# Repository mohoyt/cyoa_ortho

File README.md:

# CYOA (Choose Your Own Adventure) Ortho

CYOA Ortho or Choose Your Own Adventure Ortho is a simple Pro Micro compatible ortho PCB that you can freely adjust to your preferences by snapping off rows or columns to make your perfect Ortho board. 

The board is a 5 row x 12 column board to begin with but with the perforations on the board you can make it almost any size down to 3 x 3. So you can build ortho layouts like the Preonic (5x12), Planck (4x12), Gherkin (3x10) or even a macro or num pad.

If you go with a 4 or a 5 row variant then you have the option to have 1 or 2 2u keys on the bottom row too.

A single optional rotary encoder can be added in one of 8 positions. Supports MX or choc v1 (and v2 (since CYOA v0.4)) switches. 

See the KLE layout here: [http://www.keyboard-layout-editor.com/#/gists/a172a36ed405e7bec95fd89415a75808](http://www.keyboard-layout-editor.com/#/gists/a172a36ed405e7bec95fd89415a75808)

## Where to get one

Limited PCBs are available at STHLM kb: [https://sthlmkb.com/shop/cyoa-ortho/](https://sthlmkb.com/shop/cyoa-ortho/)

## Build instructions

These are printed on the PCB. The build is pretty simple.

1. Decide what size board you want
2. Carefully snap along perforations on PCB. It helps to use a flush cutter to help start at each end and then to use the edge of a table to assist with bending and snapping. FR4 is sharp so be careful and make sure to sand or file the edges to smoothen them
3. Solder the diodes (either side is technically fine) just make sure that you have the right orientation for them. The black stripe on the diode should line up with the white stripe on the top of the board
4. Solder the 2 switches directly above the controller. Trim the pins and isolate them with electrical tape after so that they do not short on the controller.
5. Flash and solder the controller onto the board. You want the controller to be as close as possible to the board so that it doesn't clash with any case that you're using. Make sure to plug in the board and test all the switch contacts (e.g. with tweezers) once you have done this. 
6. Install stabilisers (if you're using them), encoder (again, if you're using one) and      switches on the rest of the board.
7. Install in case. Enjoy.  

## Flashing instructions

See the firmware folder for more information.

There are example qmk files for 5x12 and 4x12 layouts for both QMK and Vial setups. These will need to be compiled using QMK or the Vial fork of Vial respectively. The `info.json` file contains all possible layouts so it should be possible to easily craft your layout using that as a starting point. 

## Plates

The CYOA Ortho is a bare PCB with no plate. It is theoretically possible to make a plate for it, and probably not hard either since it is a grid. A plate for a Planck or a Preonic could also be used if you have the same size.

## Cases

3d printed cases are available for CYOA Ortho. See here for more details: [https://www.printables.com/model/784492-cyoa-choose-your-own-adventure-ortho-keyboard-case](https://www.printables.com/model/784492-cyoa-choose-your-own-adventure-ortho-keyboard-case) These are tray style and attach to the M2 holes on the PCB. Cases are available for all possible size variations.

## Changelog / known issues

- Version 0.1 had the wrong size Pro Micro footprint. This is updated in v0.2
- Version 0.2 had a trace not connected fully meaning that the four leftmost keys on the 4th row would not work. This is fixed in version 0.3
- Version 0.4 now has larger centre holes for Choc v2 switches (currently untested though)

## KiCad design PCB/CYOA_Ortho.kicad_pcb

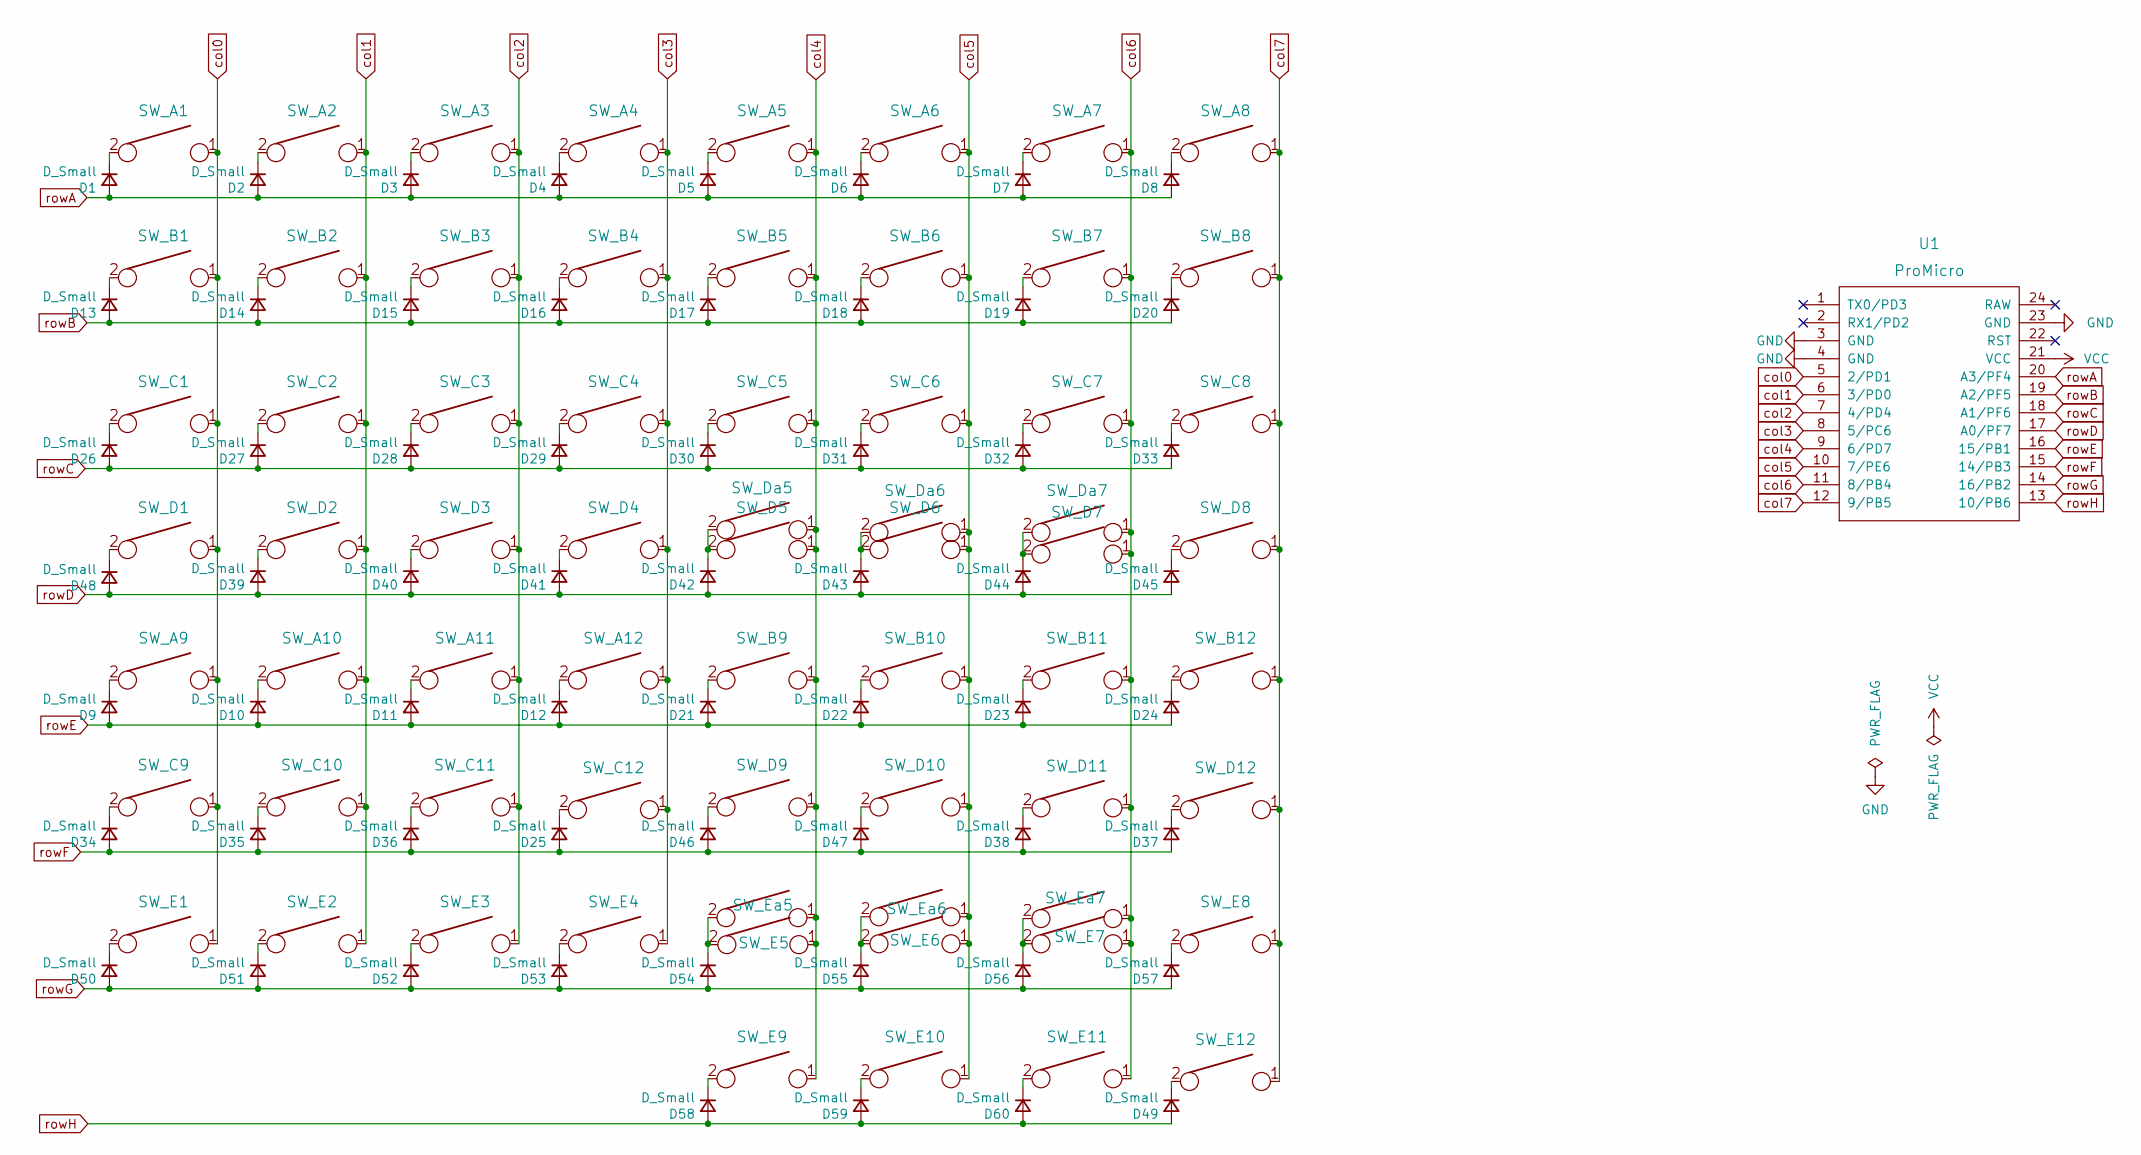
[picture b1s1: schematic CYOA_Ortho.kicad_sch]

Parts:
D1, D2, D3, D4, D5, D6, D7, D8, D9, D10, D11, D12, D13, D14, D15, D16, D17, D18, D19, D20, D21, D22, D23, D24, D25, D26, D27, D28, D29, D30, D31, D32, D33, D34, D35, D36, D37, D38, D39, D40, D41, D42, D43, D44, D45, D46, D47, D48, D49, D50, D51, D52, D53, D54, D55, D56, D57, D58, D59, D60: D_Small; Diode-Hybrid-Back
SW_A1, SW_A2, SW_A3, SW_A4, SW_A5, SW_A6, SW_A7, SW_A8, SW_A9, SW_A10, SW_A11, SW_A12: KEYSW; MX-Alps-Choc-1U-NoLED
SW_B1, SW_B2, SW_B3, SW_B4, SW_B5, SW_B6, SW_B7, SW_B8, SW_B9, SW_B10, SW_B11, SW_B12: KEYSW; MX-Alps-Choc-1U-NoLED
SW_C1, SW_C2, SW_C3, SW_C4, SW_C5, SW_C6, SW_C7, SW_C8, SW_C9, SW_C10, SW_C11, SW_C12: KEYSW; MX-Alps-Choc-1U-NoLED
SW_D1, SW_D2, SW_D3, SW_D4, SW_D5, SW_D6, SW_D7, SW_D8, SW_D9, SW_D10, SW_D11, SW_D12: KEYSW; MX-Alps-Choc-1U-NoLED
SW_Da5, SW_Da6, SW_Da7: KEYSW; MX-Alps-Choc-2U-StabFlip-NoLED
SW_E1, SW_E2, SW_E3, SW_E4, SW_E5, SW_E6, SW_E7, SW_E8, SW_E9, SW_E10, SW_E11, SW_E12: KEYSW; MX-Alps-Choc-1U-NoLED
SW_Ea5, SW_Ea6, SW_Ea7: KEYSW; MX-Alps-Choc-2U-StabFlip-NoLED
U1: ProMicro; ArduinoProMicro-Mini-USB

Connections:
GND: U1.3 (GND), U1.4 (GND), U1.23 (GND)
unnamed: D1.1 (K), SW_A1.2
unnamed: D2.1 (K), SW_A2.2
unnamed: D3.1 (K), SW_A3.2
unnamed: D4.1 (K), SW_A4.2
unnamed: D5.1 (K), SW_A5.2
unnamed: D6.1 (K), SW_A6.2
unnamed: D7.1 (K), SW_A7.2
unnamed: D8.1 (K), SW_A8.2
unnamed: D9.1 (K), SW_A9.2
unnamed: D10.1 (K), SW_A10.2
unnamed: D11.1 (K), SW_A11.2
unnamed: D12.1 (K), SW_A12.2
unnamed: D13.1 (K), SW_B1.2
unnamed: D14.1 (K), SW_B2.2
unnamed: D15.1 (K), SW_B3.2
unnamed: D16.1 (K), SW_B4.2
unnamed: D17.1 (K), SW_B5.2
unnamed: D18.1 (K), SW_B6.2
unnamed: D19.1 (K), SW_B7.2
unnamed: D20.1 (K), SW_B8.2
unnamed: D21.1 (K), SW_B9.2
unnamed: D22.1 (K), SW_B10.2
unnamed: D23.1 (K), SW_B11.2
unnamed: D24.1 (K), SW_B12.2
unnamed: D25.1 (K), SW_C12.2
unnamed: D26.1 (K), SW_C1.2
unnamed: D27.1 (K), SW_C2.2
unnamed: D28.1 (K), SW_C3.2
unnamed: D29.1 (K), SW_C4.2
unnamed: D30.1 (K), SW_C5.2
unnamed: D31.1 (K), SW_C6.2
unnamed: D32.1 (K), SW_C7.2
unnamed: D33.1 (K), SW_C8.2
unnamed: D34.1 (K), SW_C9.2
unnamed: D35.1 (K), SW_C10.2
unnamed: D36.1 (K), SW_C11.2
unnamed: D37.1 (K), SW_D12.2
unnamed: D38.1 (K), SW_D11.2
unnamed: D39.1 (K), SW_D2.2
unnamed: D40.1 (K), SW_D3.2
unnamed: D41.1 (K), SW_D4.2
unnamed: D42.1 (K), SW_D5.2, SW_Da5.2
unnamed: D43.1 (K), SW_D6.2, SW_Da6.2
unnamed: D44.1 (K), SW_D7.2, SW_Da7.2
unnamed: D45.1 (K), SW_D8.2
unnamed: D46.1 (K), SW_D9.2
unnamed: D47.1 (K), SW_D10.2
unnamed: D48.1 (K), SW_D1.2
unnamed: D49.1 (K), SW_E12.2
unnamed: D50.1 (K), SW_E1.2
unnamed: D51.1 (K), SW_E2.2
unnamed: D52.1 (K), SW_E3.2
unnamed: D53.1 (K), SW_E4.2
unnamed: D54.1 (K), SW_E5.2, SW_Ea5.2
unnamed: D55.1 (K), SW_E6.2, SW_Ea6.2
unnamed: D56.1 (K), SW_E7.2, SW_Ea7.2
unnamed: D57.1 (K), SW_E8.2
unnamed: D58.1 (K), SW_E9.2
unnamed: D59.1 (K), SW_E10.2
unnamed: D60.1 (K), SW_E11.2
VCC: U1.21 (VCC)
col0: SW_A1.1, SW_A9.1, SW_B1.1, SW_C1.1, SW_C9.1, SW_D1.1, SW_E1.1, U1.5 (2/PD1)
col1: SW_A2.1, SW_A10.1, SW_B2.1, SW_C2.1, SW_C10.1, SW_D2.1, SW_E2.1, U1.6 (3/PD0)
col2: SW_A3.1, SW_A11.1, SW_B3.1, SW_C3.1, SW_C11.1, SW_D3.1, SW_E3.1, U1.7 (4/PD4)
col3: SW_A4.1, SW_A12.1, SW_B4.1, SW_C4.1, SW_C12.1, SW_D4.1, SW_E4.1, U1.8 (5/PC6)
col4: SW_A5.1, SW_B5.1, SW_B9.1, SW_C5.1, SW_D5.1, SW_D9.1, SW_Da5.1, SW_E5.1, SW_E9.1, SW_Ea5.1, U1.9 (6/PD7)
col5: SW_A6.1, SW_B6.1, SW_B10.1, SW_C6.1, SW_D6.1, SW_D10.1, SW_Da6.1, SW_E6.1, SW_E10.1, SW_Ea6.1, U1.10 (7/PE6)
col6: SW_A7.1, SW_B7.1, SW_B11.1, SW_C7.1, SW_D7.1, SW_D11.1, SW_Da7.1, SW_E7.1, SW_E11.1, SW_Ea7.1, U1.11 (8/PB4)
col7: SW_A8.1, SW_B8.1, SW_B12.1, SW_C8.1, SW_D8.1, SW_D12.1, SW_E8.1, SW_E12.1, U1.12 (9/PB5)
rowA: D1.2 (A), D2.2 (A), D3.2 (A), D4.2 (A), D5.2 (A), D6.2 (A), D7.2 (A), D8.2 (A), U1.20 (A3/PF4)
rowB: D13.2 (A), D14.2 (A), D15.2 (A), D16.2 (A), D17.2 (A), D18.2 (A), D19.2 (A), D20.2 (A), U1.19 (A2/PF5)
rowC: D26.2 (A), D27.2 (A), D28.2 (A), D29.2 (A), D30.2 (A), D31.2 (A), D32.2 (A), D33.2 (A), U1.18 (A1/PF6)
rowD: D39.2 (A), D40.2 (A), D41.2 (A), D42.2 (A), D43.2 (A), D44.2 (A), D45.2 (A), D48.2 (A), U1.17 (A0/PF7)
rowE: D9.2 (A), D10.2 (A), D11.2 (A), D12.2 (A), D21.2 (A), D22.2 (A), D23.2 (A), D24.2 (A), U1.16 (15/PB1)
rowF: D25.2 (A), D34.2 (A), D35.2 (A), D36.2 (A), D37.2 (A), D38.2 (A), D46.2 (A), D47.2 (A), U1.15 (14/PB3)
rowG: D50.2 (A), D51.2 (A), D52.2 (A), D53.2 (A), D54.2 (A), D55.2 (A), D56.2 (A), D57.2 (A), U1.14 (16/PB2)
rowH: D49.2 (A), D58.2 (A), D59.2 (A), D60.2 (A), U1.13 (10/PB6)

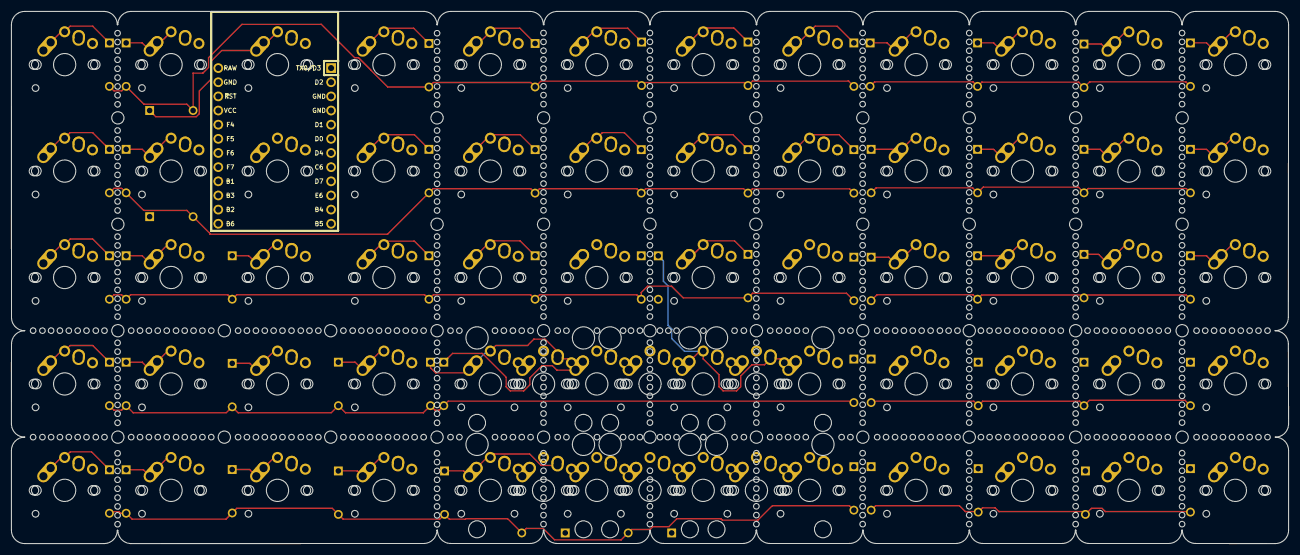
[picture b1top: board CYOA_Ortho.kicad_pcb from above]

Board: 2 copper layers, 229.2 x 95.5 mm, 127 parts (1 on the bottom side), 77 nets.

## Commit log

2023-02-02 kicad project started
2023-02-02 submodule update
2023-02-02 schematic mostly done
2023-02-05 schematic improvements
2023-02-05 schematic done, layout started
2023-10-09 Slight cleanup
2024-01-08 Layout done, routing started
2024-01-09 routing pretty much done
2024-01-09 Silkscreen mostly done
2024-01-11 Version 0.1 done and sent to fabrication
2024-01-31 Pro micro footprint fixed v0.2 done
2024-01-31 Pro micro footprint tweaked slightly to clean up front silkscreen
2024-01-31 v0.2 gerbers updated
2024-02-03 Readme and ground plane updated
2024-02-03 Readme picture updated
2024-02-05 Added some missing M2 mounting holes near the controller and updated v0.2
2024-02-13 Readme updaated and firmware added
2024-02-13 Readme updaated again
2024-02-26 Readme updated
2024-02-28 Firmware updated and photos and readme finalised for initial launch
2024-02-28 Added details on where to get them
2024-02-29 KLE layout added
2024-03-28 Version 0.3 with fixed trace issue
2024-06-18 Examples with RGB lights in place of the encoder added to firmware
2024-06-18 Fix broken image
2024-08-30 Schematic pdf and images added
2024-12-02 Updated readme to highlight lack of support for choc v2 switches
2025-01-24 Update to Kicad v8 and enlarged centre hole of switch to support Choc v2 switches too (this is in v0.4)
2025-01-24 Readme updated with v0.4 info
2025-04-09 New firmware examples added
2025-04-09 uf2 5x12 Vial compatible file added
2025-04-11 Firmware doc tweaks
2025-04-13 New no encoder 5x12 firmware files added
2025-07-27 New precompiled firmware for 4x12 no encoder git pudh
